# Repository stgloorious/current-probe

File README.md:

# Low-Noise Amplifier for Current Sensing

This is an experimental breakout board for the ultralow noise AD8331
variable-gain amplifier with internal low-noise preamplifier. 

- AC-coupled input up to 200 mV
- Adjustable gain amplifier, up to 55 dB
- Galvanically isolated output
- Single 3.3V supply

The input impedance of the amplifier should be around 6k ohms.
The probe is designed to be in close proximity (< 10 mm) to the signal source,
i.e., such that no shielded cable is required on the input side.
Instead, short wires can directly be soldered to the probe.
The output is matched to 50 ohms over an isolating signal transformer, which
connects to the SMA connector.

The amplifier module is intended to be used as a current probe with
an additional shunt resistor. The amplifier is placed near the device 
under test and amplifies the voltage drop across the measurement resistor.
The output signal is digitized by an oscilloscope connected over the SMA connector.

## Progress

- [x] Schematics design
- [x] PCB layout
- [x] PCB prototype manufacturing
- [x] In-circuit verification
- [ ] Proof-of-concept of power analysis side channel attack

### Known Issues
Although there is a notch filter to suppress the parasitic switching frequency
of the DC/DC converter, it is still visible at the output.

## Motivation
The current probe is designed to measure the transient current consumption
of microcontrollers and low-end CPUs in order to use a power consumption
side channel, which can be used to leak information about cryptographic
operations.
An example power trace measured with this current probe can be seen below.
Clearly visible are the 10 AES rounds of the AES-128-ECB algorithm running
on an STM32 microcontroller.

Such side-channel attacks have been known to exists for many years, and there
are even [commercial tools](https://chipwhisperer.readthedocs.io/en/latest/getting-started.html)
available which simplify the research process.

My goal with this DIY low-noise current probe is to have a cost-effective 
alternative to other specialized tools, as I already own 
suitable measurements equipment (i.e., an oscilloscope) 
and do not need access to other attack methods (such as fault injection).

## Manufacturing
PCB manufacturing was done in a custom panel with 5 individual PCBs by
[multi-cb](https://multi-cb.eu). Assembly was done by hand.

## License

<p xmlns:cc="http://creativecommons.org/ns#" xmlns:dct="http://purl.org/dc/terms/"><a property="dct:title" rel="cc:attributionURL" href="https://github.com/stgloorious/current-probe">current-probe</a> by <a rel="cc:attributionURL dct:creator" property="cc:attributionName" href="https://github.com/stgloorious/">Stefan Gloor</a> is licensed under <a href="http://creativecommons.org/licenses/by-sa/4.0/?ref=chooser-v1" target="_blank" rel="license noopener noreferrer" style="display:inline-block;">CC BY-SA 4.0</a></p>

This does not include work of third parties, e.g., 3D STEP models.

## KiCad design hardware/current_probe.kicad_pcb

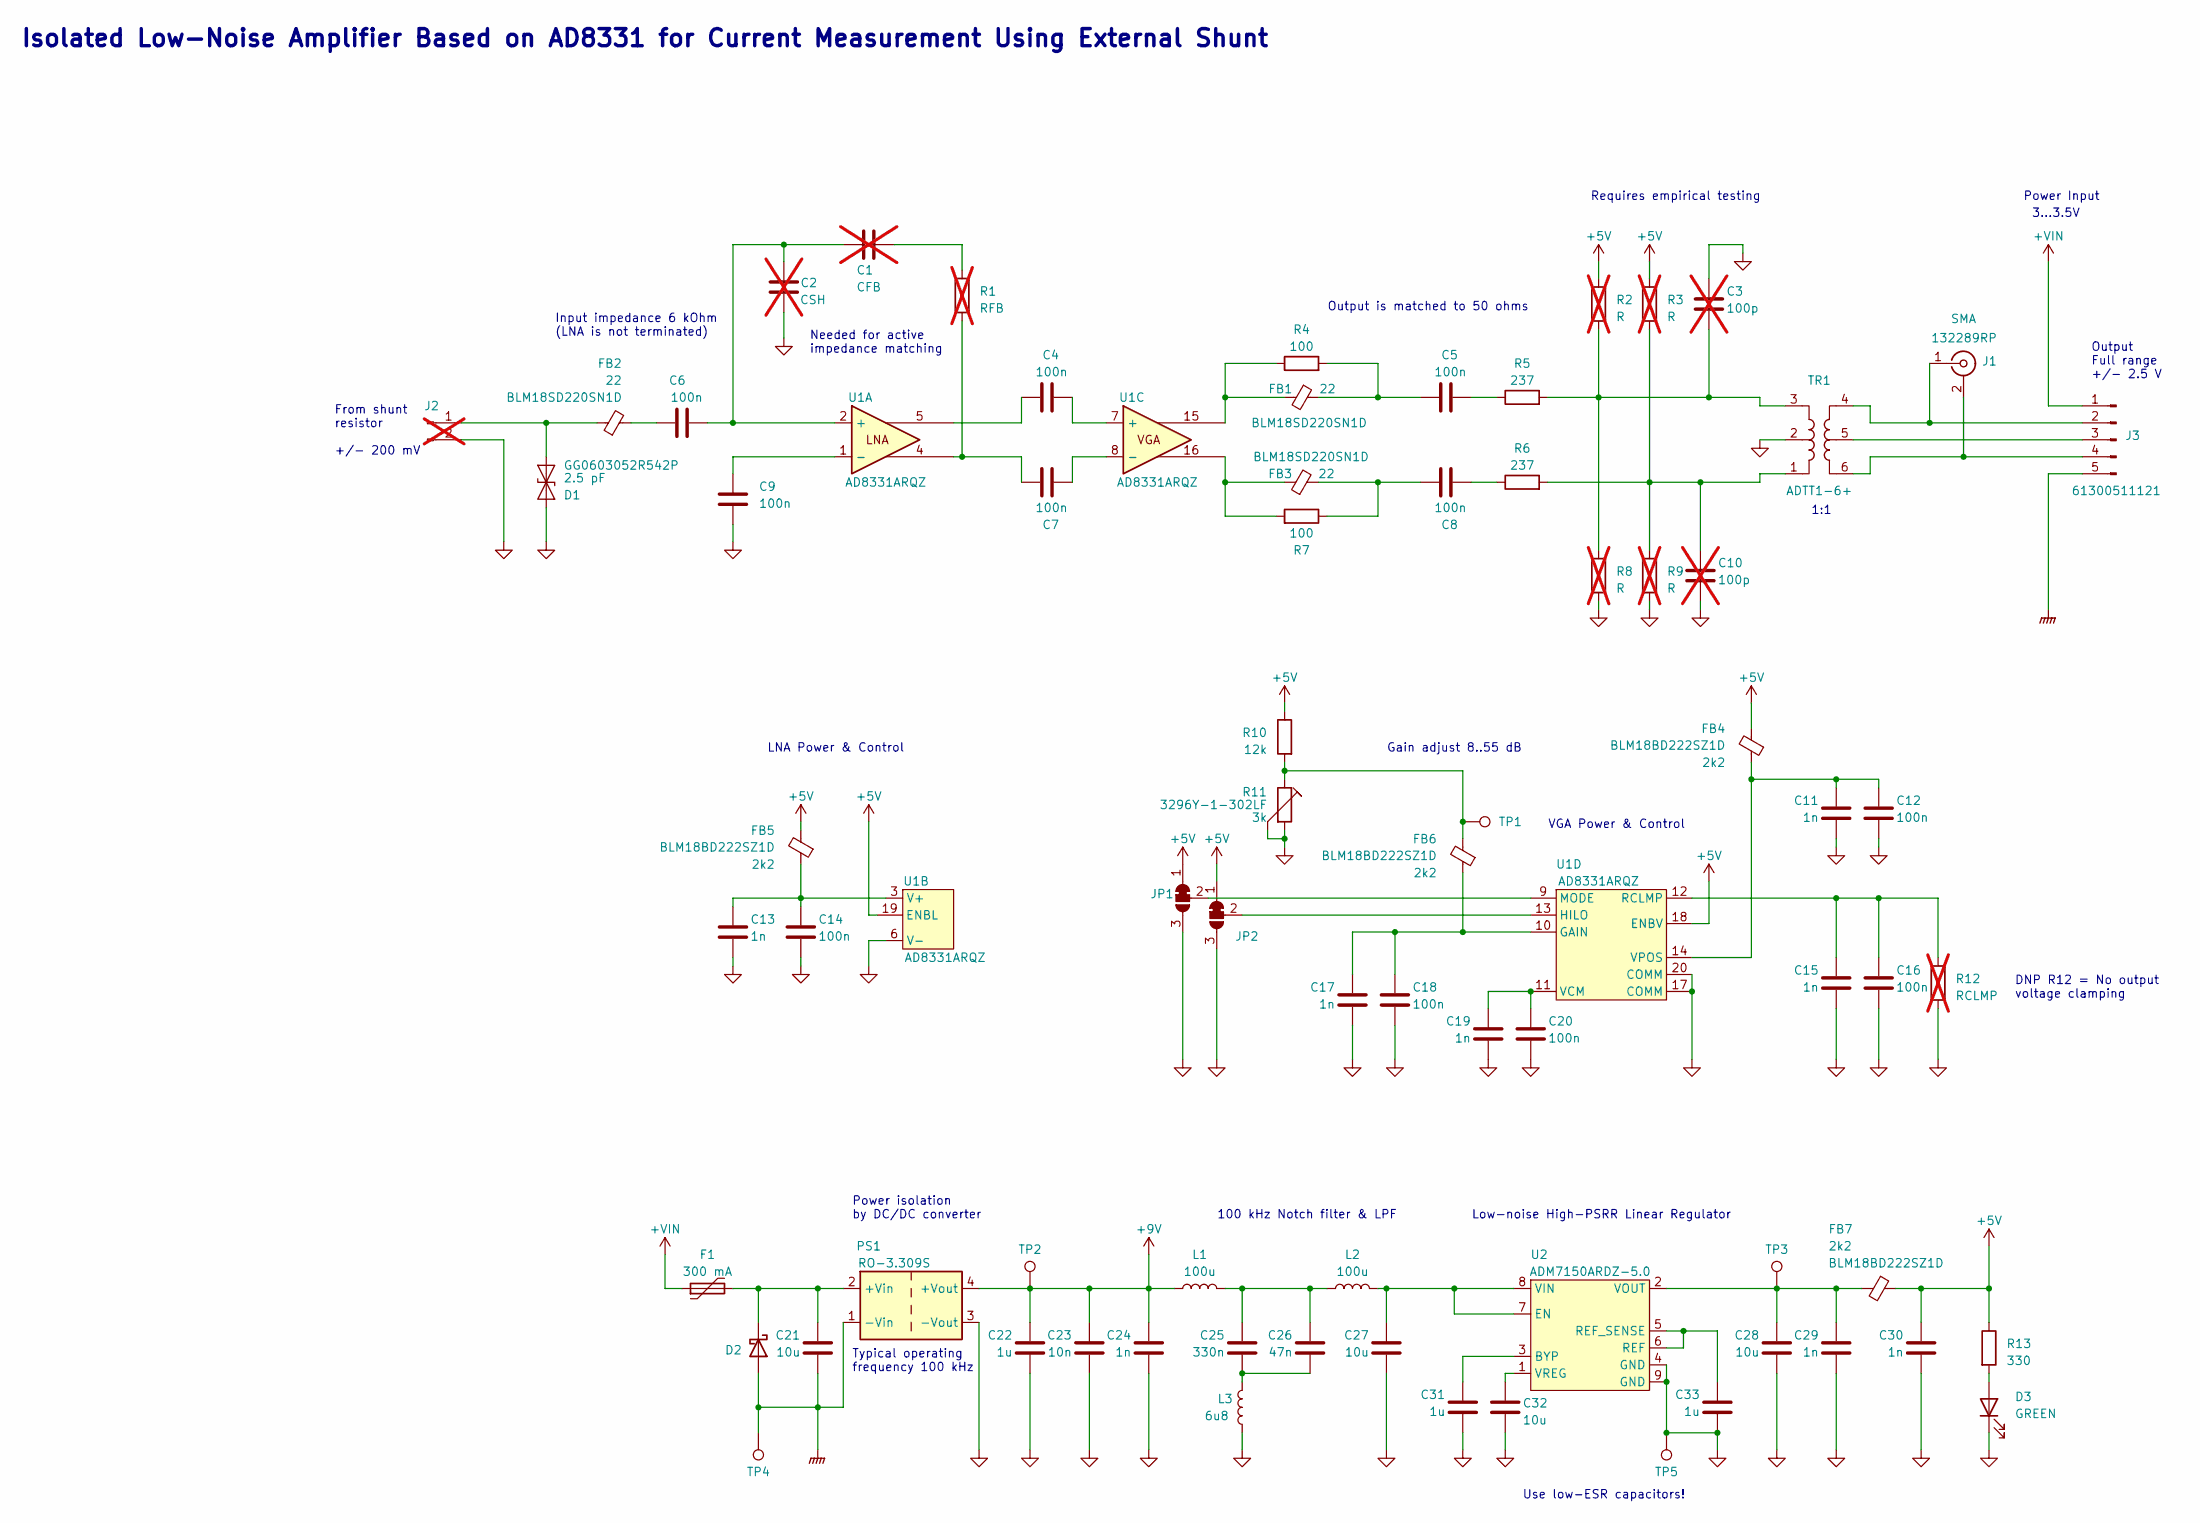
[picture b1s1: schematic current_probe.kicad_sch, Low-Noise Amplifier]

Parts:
C1: CFB; C_0603_1608Metric; not fitted
C2: CSH; C_0603_1608Metric; not fitted
C3, C10: 100p; C_0603_1608Metric; not fitted
C4, C5, C6, C7, C8, C9, C12, C14, C16, C18, C20: 100n; C_0603_1608Metric; Part CL10B104KB8WPNC
C11, C13, C15, C17, C19, C29, C30: 1n; C_0603_1608Metric; Part CL10B102KB8WPNC
C21, C27, C28, C32: 10u; C_0805_2012Metric; Part GCM21BR71A106KE22L
C22, C31, C33: 1u; C_0805_2012Metric; Part GCM21BR71H105MA03L
C23: 10n; C_0603_1608Metric; Part CL10B103KB8WPNC
C24: 1n; C_0603_1608Metric
C25: 330n; C_0603_1608Metric; Part CGA3E3X7R1H334K080AB
C26: 47n; C_0603_1608Metric; Part CGA3E2X7R1H473K080AA
D1: 2.5 pF; D_0603_1608Metric; Part GG0603052R542P
D2: D_Schottky; D_SMA; Part SK510A-LTP
D3: GREEN; LED_0805_2012Metric; Part SML-LXT0805GW-TR
F1: 300 mA; Fuse_0805_2012Metric; Part 0805L010/24YR
FB1, FB2, FB3: 22; L_0603_1608Metric; Part BLM18SD220SN1D
FB4, FB5, FB6, FB7: 2k2; L_0603_1608Metric; Part BLM18BD222SZ1D
J1: SMA; SMA_Amphenol_132289_EdgeMount; Part 132289RP
J2: Conn_01x02_Pin; PinHeader_1x02_P2.54mm_Horizontal; not fitted
J3: Conn_01x05_Pin; PinHeader_1x05_P2.54mm_Vertical; Part 61300511121
JP1, JP2: SolderJumper_3_Bridged12; SolderJumper-3_P1.3mm_Bridged12_Pad1.0x1.5mm
L1, L2: 100u; L_0805_2012Metric; Part MLZ2012N101LT000
L3: 6u8; L_0805_2012Metric; Part MLZ2012N6R8LT000
PS1: RO-3.309S; Converter_DCDC_Murata_MEE1SxxxxSC_THT; Part RO-3.309S
R1: RFB; R_0603_1608Metric; not fitted
R2, R3, R8, R9: R; R_0603_1608Metric; not fitted
R4, R7: 100; R_0603_1608Metric; Part RS73F1JTTD1000B
R5, R6: 237; R_0603_1608Metric; Part ERJ-PB3B2370V
R10: 12k; R_0603_1608Metric; Part AC0603FR-0712KL
R11: 3k; Potentiometer_Bourns_3296Y_Vertical; Part 3296Y-1-302LF
R12: RCLMP; R_0603_1608Metric; not fitted
R13: 330; R_0603_1608Metric; Part RMCF0603FT330R
TP1, TP2, TP3, TP4, TP5: TestPoint; TestPoint_Loop_D1.80mm_Drill1.0mm_Beaded; Part 5001
TR1: ADTT1-6+; Mini-Circuits_CD637_H5.23mm; Part ADTT1-6+
U1: AD8331ARQZ; RQ_20_ADI-L; Part AD8331ARQZ
U2: ADM7150ARDZ-5.0; SOIC-8-1EP_3.9x4.9mm_P1.27mm_EP2.29x3mm; Part ADM7150ARDZ-5.0

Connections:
+5V: C30.2, FB4.2, FB5.2, FB7.1, JP1.1 (A), JP2.1 (A), R2.1, R3.1, R10.1, R13.1, U1.18 (ENBV), U1.19 (ENBL)
+9V: C22.2, C23.2, C24.2, L1.1, PS1.4 (+Vout), TP2.1
+VIN: F1.1, J3.1
GND: C2.2, C3.2, C9.2, C10.1, C11.1, C12.1, C13.1, C14.1, C15.1, C16.1, C17.1, C18.1, C19.1, C20.1, C22.1, C23.1, C24.1, C27.1, C28.1, C29.1, C30.1, C31.1, C32.1, C33.1, D1.2 (A2), D3.1 (K), J2.2, JP1.3 (B), JP2.3 (B), L3.1, PS1.3 (-Vout), R8.2, R9.2, R11.2, R11.3, R12.2, TP5.1, TR1.2, U1.6 (V-), U1.17 (COMM), U1.20 (COMM), U2.4 (GND), U2.9 (GND)
GNDPWR: C21.1, D2.2 (A), J3.5, PS1.1 (-Vin), TP4.1
unnamed: C1.2, R1.1
unnamed: C3.1, R2.2, R5.2, R8.1, TR1.3
unnamed: C4.2, U1.5
unnamed: C5.1, R5.1
unnamed: C5.2, FB1.1, R4.2
unnamed: C6.2, FB2.2
unnamed: C7.2, R1.2, U1.4
unnamed: C8.1, R6.1
unnamed: C8.2, FB3.2, R7.1
unnamed: C10.2, R3.2, R6.2, R9.1, TR1.1
unnamed: C25.1, C26.1, L3.2
unnamed: C25.2, C26.2, L1.2, L2.1
unnamed: D1.1 (A1), FB2.1, J2.1
unnamed: C21.2, D2.1 (K), F1.2, PS1.2 (+Vin)
unnamed: D3.2 (A), R13.2
unnamed: FB1.2, R4.1, U1.15
unnamed: FB3.1, R7.2, U1.16
unnamed: FB6.2, R10.2, R11.1, TP1.1
unnamed: J1.2 (Ext), J3.4, TR1.6
unnamed: J1.1 (In), J3.2, TR1.4
unnamed: J3.3, TR1.5
unnamed: JP1.2 (C), U1.9 (MODE)
unnamed: JP2.2 (C), U1.13 (HILO)
unnamed: C1.1, C2.1, C6.1, U1.2 (+)
unnamed: C9.1, U1.1 (-)
unnamed: C13.2, C14.2, FB5.1, U1.3 (V+)
unnamed: C4.1, U1.7 (+)
unnamed: C7.1, U1.8 (-)
unnamed: C17.2, C18.2, FB6.1, U1.10 (GAIN)
unnamed: C15.2, C16.2, R12.1, U1.12 (RCLMP)
unnamed: C19.2, C20.2, U1.11 (VCM)
unnamed: C11.2, C12.2, FB4.1, U1.14 (VPOS)
unnamed: C31.2, U2.3 (BYP)
unnamed: C27.2, L2.2, U2.7 (EN), U2.8 (VIN)
unnamed: C33.2, U2.5 (REF_SENSE), U2.6 (REF)
unnamed: C28.2, C29.2, FB7.2, TP3.1, U2.2 (VOUT)
unnamed: C32.2, U2.1 (VREG)

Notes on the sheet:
100 kHz Notch filter & LPF
From shunt resistor +/- 200 mV
LNA Power & Control
1:1
Power Input
Output Full range +/- 2.5 V
3...3.5V
DNP R12 = No output voltage clamping
Output is matched to 50 ohms
VGA Power & Control
Needed for active impedance matching
Use low-ESR capacitors!
Typical operating frequency 100 kHz
Low-noise High-PSRR Linear Regulator
Input impedance 6 kOhm (LNA is not terminated)
Gain adjust 8..55 dB
Isolated Low-Noise Amplifier Based on AD8331 for Current Measurement Using External Shunt
Requires empirical testing
Power isolation by DC/DC converter

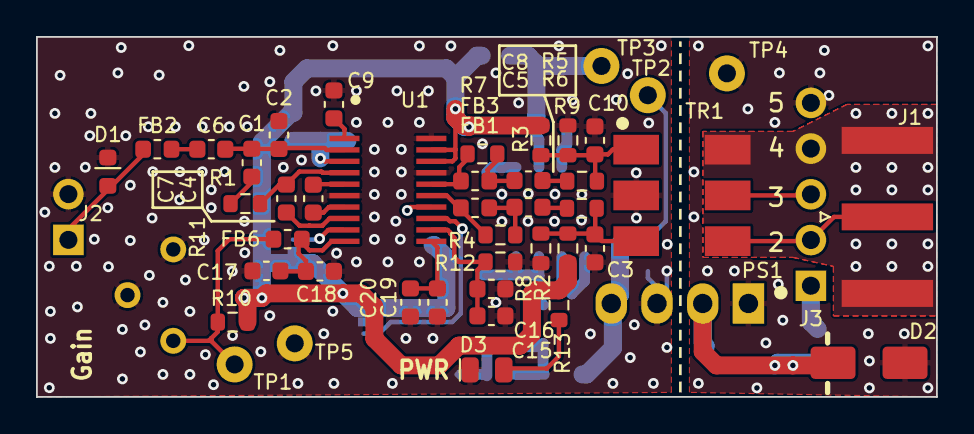
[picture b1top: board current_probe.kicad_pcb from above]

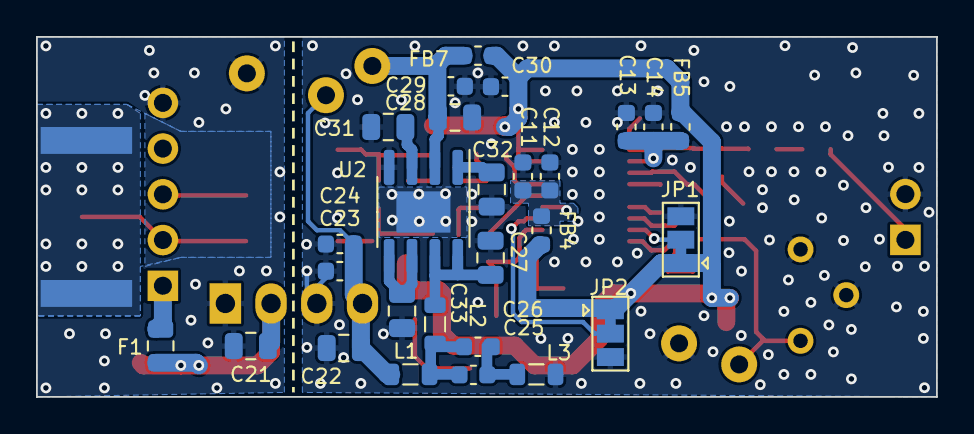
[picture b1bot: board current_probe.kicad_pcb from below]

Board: 2 copper layers, 50.0 x 20.0 mm, 74 parts (27 on the bottom side), 42 nets.

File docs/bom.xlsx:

| Bill of Materials (BOM)
 | Project: current_probe
 | Version: 11.10.2023
Item | Qty | Designators | Value | Footprint | DNP | Part Number
1 | 1 | C1 | CFB | Capacitor_SMD:C_0603_1608Metric | DNP
2 | 1 | C2 | CSH | Capacitor_SMD:C_0603_1608Metric | DNP
3 | 2 | C3, C10 | 100p | Capacitor_SMD:C_0603_1608Metric | DNP
4 | 11 | C4, C5, C6, C7, C8, C9, C12, C14, C16, C18, C20 | 100n | Capacitor_SMD:C_0603_1608Metric |  | CL10B104KB8WPNC
5 | 8 | C11, C13, C15, C17, C19, C24, C29, C30 | 1n | Capacitor_SMD:C_0603_1608Metric |  | CL10B102KB8WPNC
6 | 4 | C21, C27, C28, C32 | 10u | Capacitor_SMD:C_0805_2012Metric |  | GCM21BR71A106KE22L
7 | 3 | C22, C31, C33 | 1u | Capacitor_SMD:C_0805_2012Metric |  | GCM21BR71H105MA03L
8 | 1 | C23 | 10n | Capacitor_SMD:C_0603_1608Metric |  | CL10B103KB8WPNC
9 | 1 | C25 | 330n | Capacitor_SMD:C_0603_1608Metric |  | CGA3E3X7R1H334K080AB
10 | 1 | C26 | 47n | Capacitor_SMD:C_0603_1608Metric |  | CGA3E2X7R1H473K080AA
11 | 1 | D1 | 2.5 pF | Diode_SMD:D_0603_1608Metric |  | GG0603052R542P
12 | 1 | D2 | D_Schottky | Diode_SMD:D_SMA |  | SK510A-LTP
13 | 1 | D3 | GREEN | LED_SMD:LED_0805_2012Metric |  | SML-LXT0805GW-TR
14 | 1 | F1 | 300 mA | Fuse:Fuse_0805_2012Metric |  | 0805L010/24YR
15 | 3 | FB1, FB2, FB3 | 22 | Inductor_SMD:L_0603_1608Metric |  | BLM18SD220SN1D
16 | 4 | FB4, FB5, FB6, FB7 | 2k2 | Inductor_SMD:L_0603_1608Metric |  | BLM18BD222SZ1D
17 | 1 | J1 | SMA | Connector_Coaxial:SMA_Amphenol_132289_EdgeMount |  | 132289RP
18 | 1 | J2 | Conn_01x02_Pin | Connector_PinHeader_2.54mm:PinHeader_1x02_P2.54mm_Horizontal | DNP
19 | 1 | J3 | Conn_01x05_Pin | Connector_PinHeader_2.54mm:PinHeader_1x05_P2.54mm_Vertical |  | 61300511121
20 | 2 | L1, L2 | 100u | Inductor_SMD:L_0805_2012Metric |  | MLZ2012N101LT000
21 | 1 | L3 | 6u8 | Inductor_SMD:L_0805_2012Metric |  | MLZ2012N6R8LT000
22 | 1 | PS1 | RO-3.309S | Converter_DCDC:Converter_DCDC_Murata_MEE1SxxxxSC_THT |  | RO-3.309S
23 | 1 | R1 | RFB | Resistor_SMD:R_0603_1608Metric | DNP
24 | 4 | R2, R3, R8, R9 | R | Resistor_SMD:R_0603_1608Metric | DNP
25 | 2 | R4, R7 | 100 | Resistor_SMD:R_0603_1608Metric |  | RS73F1JTTD1000B
26 | 2 | R5, R6 | 237 | Resistor_SMD:R_0603_1608Metric |  | ERJ-PB3B2370V
27 | 1 | R10 | 12k | Resistor_SMD:R_0603_1608Metric |  | AC0603FR-0712KL
28 | 1 | R11 | 3k | Potentiometer_THT:Potentiometer_Bourns_3296Y_Vertical |  | 3296Y-1-302LF
29 | 1 | R12 | RCLMP | Resistor_SMD:R_0603_1608Metric | DNP
30 | 1 | R13 | 330 | Resistor_SMD:R_0603_1608Metric |  | RMCF0603FT330R
31 | 5 | TP1, TP2, TP3, TP4, TP5 | TestPoint | TestPoint:TestPoint_Loop_D1.80mm_Drill1.0mm_Beaded |  | 5001
32 | 1 | TR1 | ADTT1-6+ | RF_Mini-Circuits:Mini-Circuits_CD637_H5.23mm |  | ADTT1-6+
33 | 1 | U1 | AD8331ARQZ | current_probe:RQ_20_ADI-L |  | AD8331ARQZ
34 | 1 | U2 | ADM7150ARDZ-5.0 | Package_SO:SOIC-8-1EP_3.9x4.9mm_P1.27mm_EP2.29x3mm |  | ADM7150ARDZ-5.0

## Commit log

2023-10-07 Add simulations - LTspice simulation of Notch Filter and Low pass filter used inbetween DC/DC converter and linear regulator.
2023-10-07 Create gitignore
2023-10-07 Ignore certain output files which should be moved to /docs
2023-10-07 Ignore backup and temporary files
2023-10-07 Ignore ctags file
2023-10-07 Fix file path
2023-10-07 Add hardware files
2023-10-07 Add docs
2023-10-07 Add readme
2023-10-07 Update README.md
    - Fix images
    - Add licence
2023-10-07 New renderings
2023-10-07 Update README.md
    Change scaling of images
2023-10-07 Update README.md
    Wording
2023-10-07 Create LICENSE
2023-10-07 Update README.md
    Change rendering sizes
2023-10-07 Change rendering sizes
2023-10-07 Consolidate layer and assembly drawings into a single file
2023-10-08 Incorporate design review feedback - Enhance routing of input path - Remove voltage reference, used voltage divider instead for gain voltage - Made vias smaller
2023-10-08 Create panel - Create panel design with 5 amplifier PCBs - Add panel assembly drawing - Add production data
2023-10-08 Add panel image
2023-10-08 Add unit numbers to panel
2023-10-09 Tried to fix edge cuts and via sizes in panel, regenerated gerbers
2023-10-09 Fix edge cuts on panel
2023-10-11 Updated BOM and part numbers
2023-10-20 PCB assembly - updated progress - add picture
2023-10-20 Fixed broken link
2023-10-20 Introduction text
2023-10-20 Rephrasing
2023-10-20 Ignoring pictures and gimp files
2024-02-21 Add power trace and update progress; add known issues
